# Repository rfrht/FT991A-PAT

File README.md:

# Buffered IF tap board for Panadapter / SDR in a Yaesu FT-991-A

## Instructions, tests, pictures and full documentation: Check the [Wiki](https://github.com/rfrht/FT991A-PAT/wiki)

## Yaesu FT-991/A Custom Panoramic Adapter Buffered TAP Board for external SDR / Spectrum Analyser

This project is a remix of OE2DOR's [perfect and neatly crafted](https://raw.githubusercontent.com/Lightning1984/FT991A-PAT/PAT-Light/Design/FT991-PAT_Installed.jpg) FT-991/A Panadapter board with a high impedance IF tap, in order to disturb to a [minimum](https://youtu.be/yeTeMTJRBIg) the radio sensitivity.

This design is compatible with both A and non-A FT-991 transceivers.

The objective is to actually **lodge** a RTL-SDR **inside** a FT-991/A, with no extra cables coming off the radio.

The schematics are in Autodesk Eagle EDA format. Check the [Schematic](Schematic) folder. The [Design](Design) folder contains the ready to print Gerber files, images and some ancillary material.

The project genesis and some discussion are logged on QRZ Forum: [A FT-991/A IF tap for Panadapter / RTL-SDR inside the radio](https://forums.qrz.com/index.php?threads/hard-hack-embedding-a-sdr-in-ft-991a-need-rf-designers-review.650840/). If you need to ask questions, either file a Github Issue (preferred) or use the QRZ Forum.

If you are interested in build your own, [click here to download the Gerber](Design/board-gerbers.zip) and order in your favourite PCB Fab (like [JLCPCB](https://jlcpcb.com/quote), super cheap, good quality and $0 shipping on first order). **Ensure to read the [Wiki](https://github.com/rfrht/FT991A-PAT/wiki)**.

### Notes:

* The board (5 samples) costed $2 in [jlcpcb.com](https://jlcpcb.com/quote).
* The [parts](Design/bom-ft991-panadapter.csv) costs around $20 in Digi-Key.
* The IF signal is wide open, spanning the radio's [preselector filter range](/rfrht/FT991A-PAT/wiki/appendix-preselector-rx-stage-characteristics). With that comes also a problem: Very strong signals in passband might spew images through the spectrum in your SDR. Use the RTL-SDR RX gain to counteract.
* There's a Full Version with some extra bells and whistles (more details in the Wiki). Use the Branch "Rev-R-Full".

### Changelog:
Check [Here](CHANGELOG.md)

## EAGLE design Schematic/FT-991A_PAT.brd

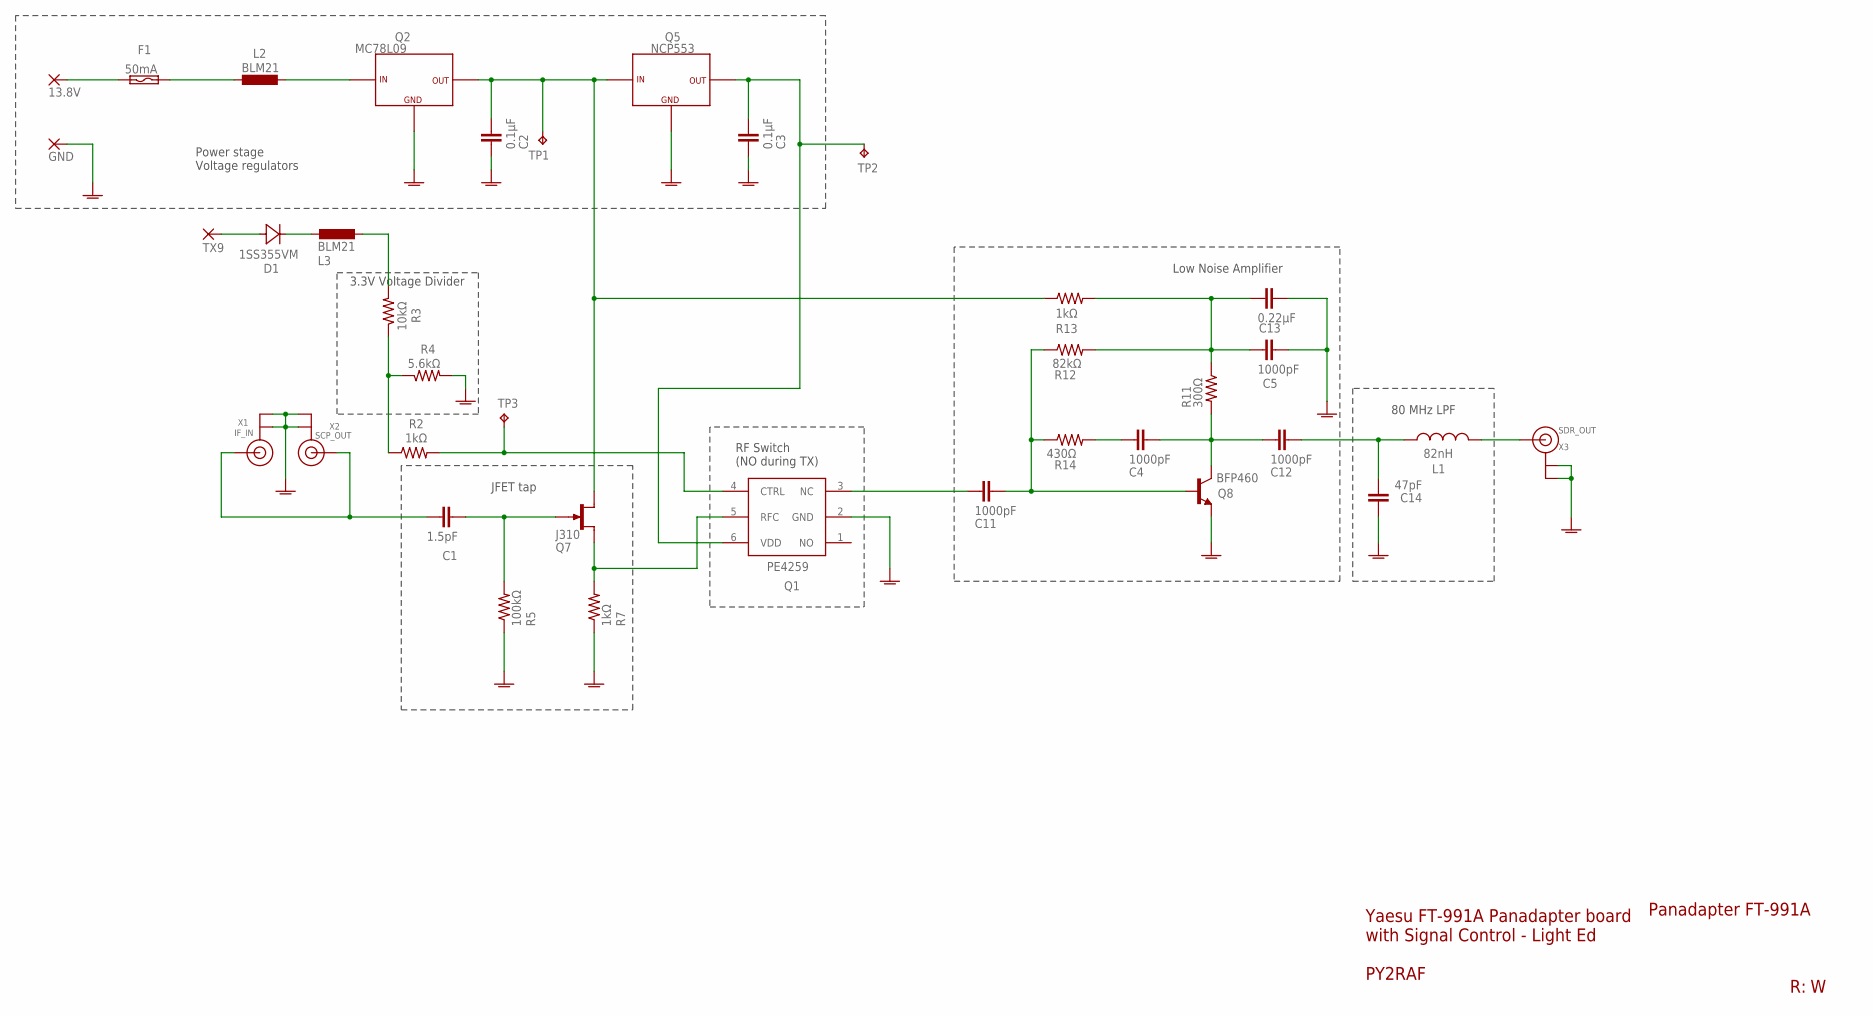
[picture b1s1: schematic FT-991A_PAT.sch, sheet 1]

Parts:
13.8V: 13.8V; SMD1,27-2,54
C1: 1.5pF; 0805
C2, C3: 0.1µF; 1206
C4, C5, C11, C12: 1000pF; 0805
C13: 0.22µF; 0805
C14: 47pF; 0805
D1: 1SS355VM; SOD-323
F1: 50mA; FUSE-1206
GND: GND; SMD1,27-2,54
L1: 82nH; 0805
L2, L3: BLM21; 0805
PAD3: TX9; SMD1,27-2,54
Q1: PE4259; SC-70
Q2: MC78L09; SOIC8
Q5: NCP553; SC-82AB
Q7: J310; SOT23-3
Q8: BFP460; SOT343R
R2, R7, R13: 1kΩ; 1206
R3: 10kΩ; 1206
R4: 5.6kΩ; 1206
R5: 100kΩ; 1206
R11: 300Ω; 1206
R12: 82kΩ; 1206
R14: 430Ω; 1206
TP1: 9V; B1,27
TP2, TP3: 3V; B1,27
X1: IF_IN; U.FL
X2: SCP_OUT; U.FL
X3: SDR_OUT; U.FL

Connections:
3V: C3.1, Q1.6 (VDD), Q5.3 (OUT), TP2.TP
9V: C2.1, Q2.1 (OUT), Q5.2 (IN), Q7.2 (S), R13.1, TP1.TP
AC-FB: C4.P$1 (1), R14.2
COLL-LOAD: C5.P$1 (1), C13.P$1 (1), R11.1, R12.2, R13.2
FINAL: L1.P$2 (2), X3.3 (SIGNAL)
GNDA: C2.2, C3.2, C5.P$2 (2), C13.P$2 (2), C14.P$1 (1), GND.1, Q1.2 (GND), Q2.2 (GN), Q2.3 (GN), Q2.6 (GN), Q2.7 (GN), Q5.1 (GN), Q8.1 (E), Q8.3 (E), R4.2, R5.1, R7.1, X1.1 (GND), X1.2 (GND), X2.1 (GND), X2.2 (GND), X3.1 (GND), X3.2 (GND)
IF-IN: C1.P$1 (1), X1.3 (SIGNAL), X2.3 (SIGNAL)
JFET-IN: C1.P$2 (2), Q7.3 (G), R5.2
JFET-OUT: Q1.5 (RFC), Q7.1 (D), R7.2
LNA-IN: C11.P$2 (2), Q8.4 (B), R12.1, R14.1
LNA-OUT: C4.P$2 (2), C12.P$1 (1), Q8.2 (C), R11.2
LPF-80M: C12.P$2 (2), C14.P$2 (2), L1.P$1 (1)
unnamed: R2.1, R3.1, R4.1
unnamed: L3.P$2 (2), R3.2
unnamed: L2.P$1 (1), Q2.8 (IN)
unnamed: 13.8V.1, F1.1
unnamed: F1.2, L2.P$2 (2)
unnamed: D1.C, L3.P$1 (1)
SW-OUT: C11.P$1 (1), Q1.3 (NC)
SW_FLIP: Q1.4 (CTRL), R2.2, TP3.TP
TX9: D1.A, PAD3.1

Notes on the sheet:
Panadapter FT-991A
PY2RAF
Yaesu FT-991A Panadapter board with Signal Control - Light Ed
3.3V Voltage Divider
Low Noise Amplifier
Power stage Voltage regulators
RF Switch (NO during TX)
JFET tap
80 MHz LPF

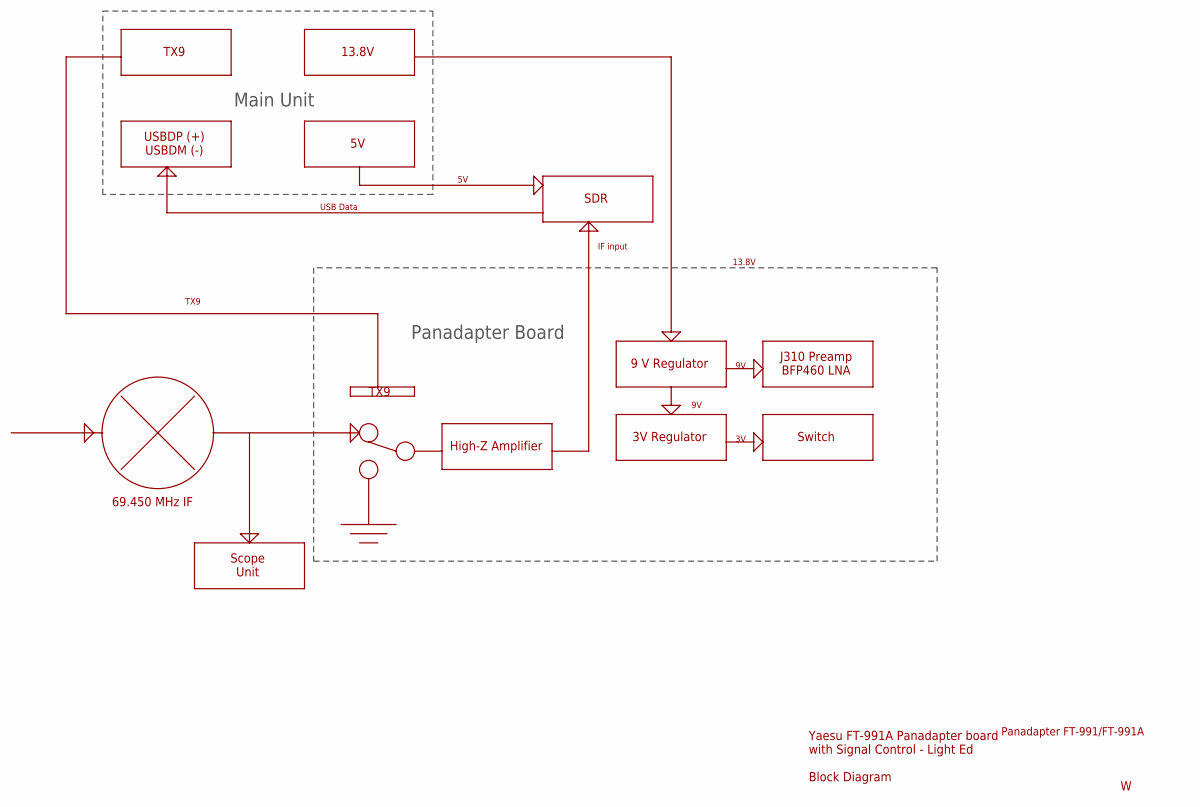
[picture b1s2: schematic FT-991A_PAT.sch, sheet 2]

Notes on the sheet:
Scope Unit
TX9
69.450 MHz IF
SDR
13.8V
Main Unit
Panadapter Board
IF input
Panadapter FT-991/FT-991A
Yaesu FT-991A Panadapter board with Signal Control - Light Ed Block Diagram
USBDP (+) USBDM (-)
USB Data
High-Z Amplifier
9 V Regulator
3V Regulator
J310 Preamp BFP460 LNA
Switch

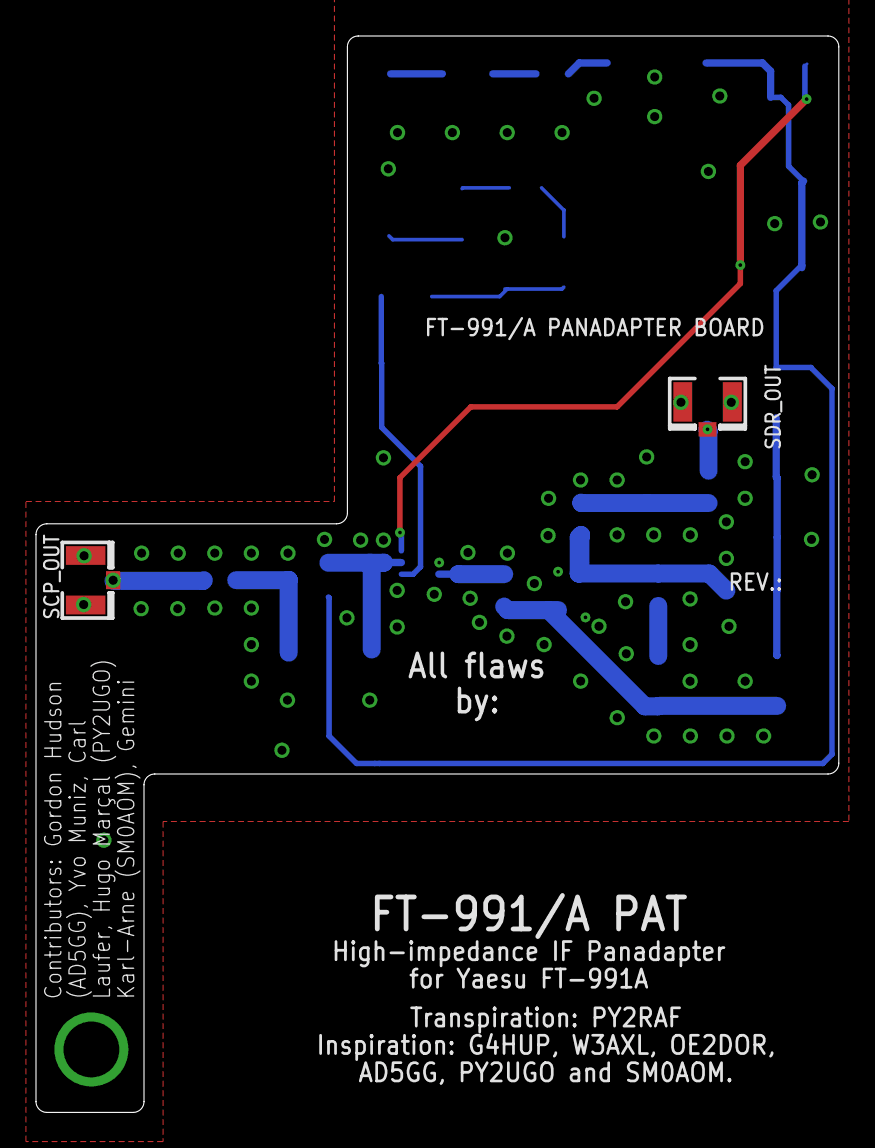
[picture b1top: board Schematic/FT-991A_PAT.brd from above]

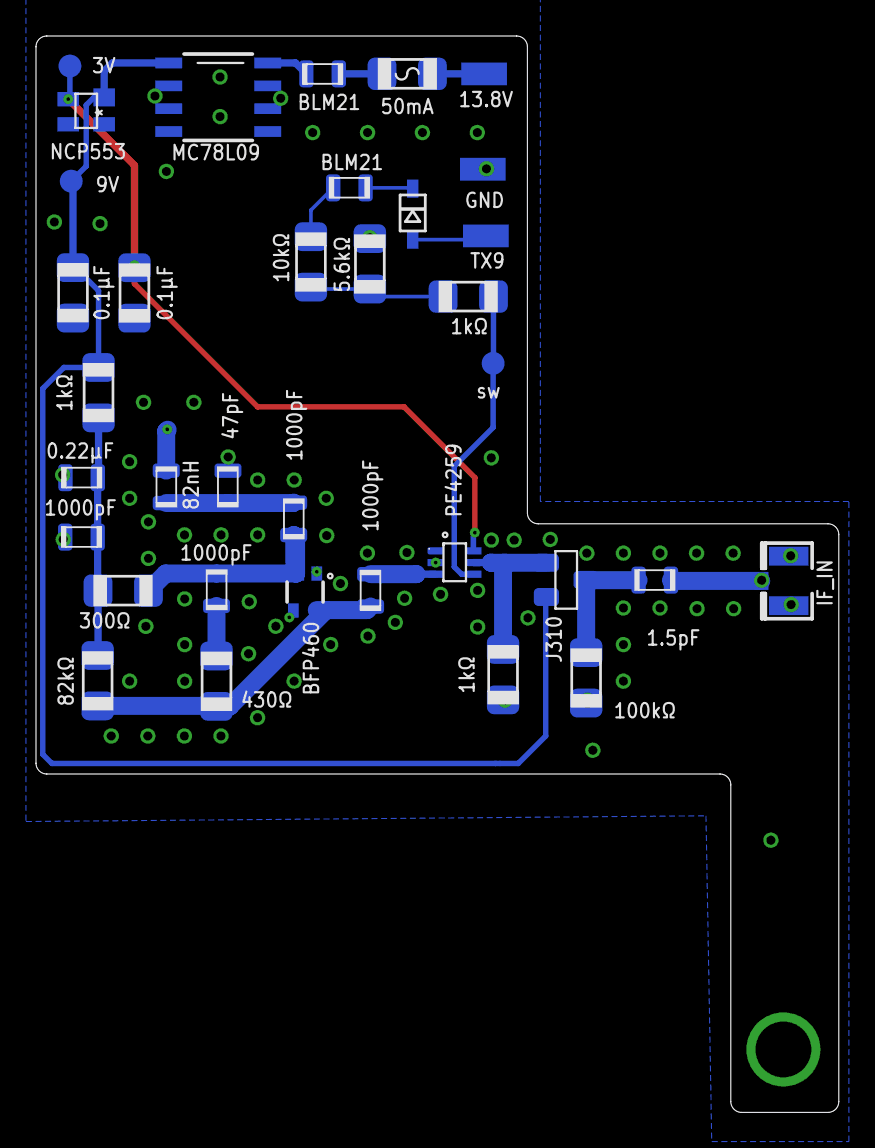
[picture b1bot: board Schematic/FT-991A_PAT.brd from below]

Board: 2 copper layers, 44.6 x 59.8 mm, 37 parts (35 on the bottom side), 21 nets.

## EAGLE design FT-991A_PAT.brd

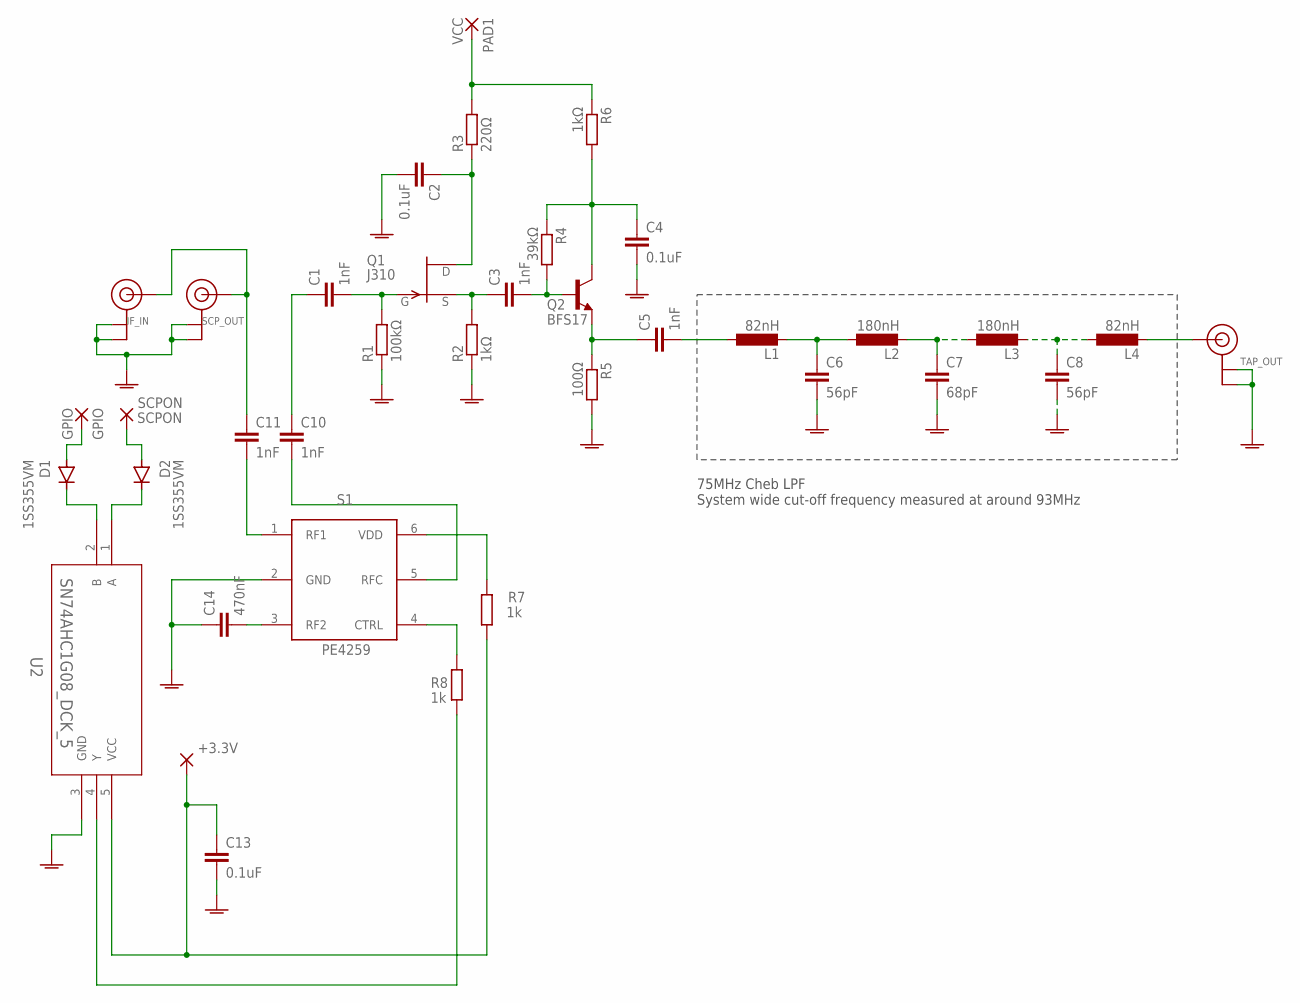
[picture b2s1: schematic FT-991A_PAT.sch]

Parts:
+3.3V: WIREPADSMD1,27-254; SMD1,27-2,54
C1, C3, C5, C10, C11: 1nF; C0805K
C2, C4, C13: 0.1uF; C0805K
C6, C8: 56pF; C0805K
C7: 68pF; C0805K
C14: 470nF; C0805K
D1, D2: 1SS355VM; SOD323-W
GPIO: GPIO; SMD1,27-2,54
L1, L4: 82nH; L0805
L2, L3: 180nH; L0805
PAD1: VCC; SMD2,54-5,08
Q1: J310; SOT23
Q2: BFS17; SOT23
R1: 100kΩ; R0805
R2: 1kΩ; R0805
R3: 220Ω; R0805
R4: 39kΩ; R0805
R5: 100Ω; R0805
R6: 1kΩ; R1206
R7, R8: 1k; R0805
S1: PE4259; SC-70
SCPON: SCPON; SMD1,27-2,54
TAP_OUT: TAP_OUT; U.FL
U2: SN74AHC1G08_DCK_5; DCK5
X1: SCP_OUT; U.FL
X2: IF_IN; U.FL

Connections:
GNDA: C2.2, C4.2, C6.2, C7.2, C8.2, C13.2, C14.1, R1.1, R2.1, R5.2, S1.2 (GND), TAP_OUT.1 (GND), TAP_OUT.2 (GND), U2.3 (GND), X1.1 (GND), X1.2 (GND), X2.1 (GND), X2.2 (GND)
unnamed: C5.1, Q2.2 (E), R5.1
unnamed: C5.2, L1.1
unnamed: C6.1, L1.2, L2.1
unnamed: C3.2, Q2.1 (B), R4.2
unnamed: C3.1, Q1.2 (S), R2.2
unnamed: C1.2, Q1.3 (G), R1.2
unnamed: C11.1, X1.3 (SIGNAL), X2.3 (SIGNAL)
unnamed: PAD1.1, R3.2, R6.1
unnamed: C2.1, Q1.1 (D), R3.1
unnamed: C4.1, Q2.3 (C), R4.1, R6.2
unnamed: C7.1, L2.2, L3.1
unnamed: L4.2, TAP_OUT.3 (SIGNAL)
unnamed: C8.1, L3.2, L4.1
unnamed: C1.1, C10.1
unnamed: C10.2, S1.5 (RFC)
unnamed: D1.A, GPIO.1
unnamed: D1.C, U2.2 (B)
unnamed: D2.A, SCPON.1
unnamed: R8.2, S1.4 (CTRL)
unnamed: D2.C, U2.1 (A)
unnamed: C11.2, S1.1 (RF1)
unnamed: R8.1, U2.4 (Y)
unnamed: C14.2, S1.3 (RF2)
VCC: +3.3V.1, C13.1, R7.1, U2.5 (VCC)
VDD: R7.2, S1.6 (VDD)

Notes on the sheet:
75MHz Cheb LPF System wide cut-off frequency measured at around 93MHz

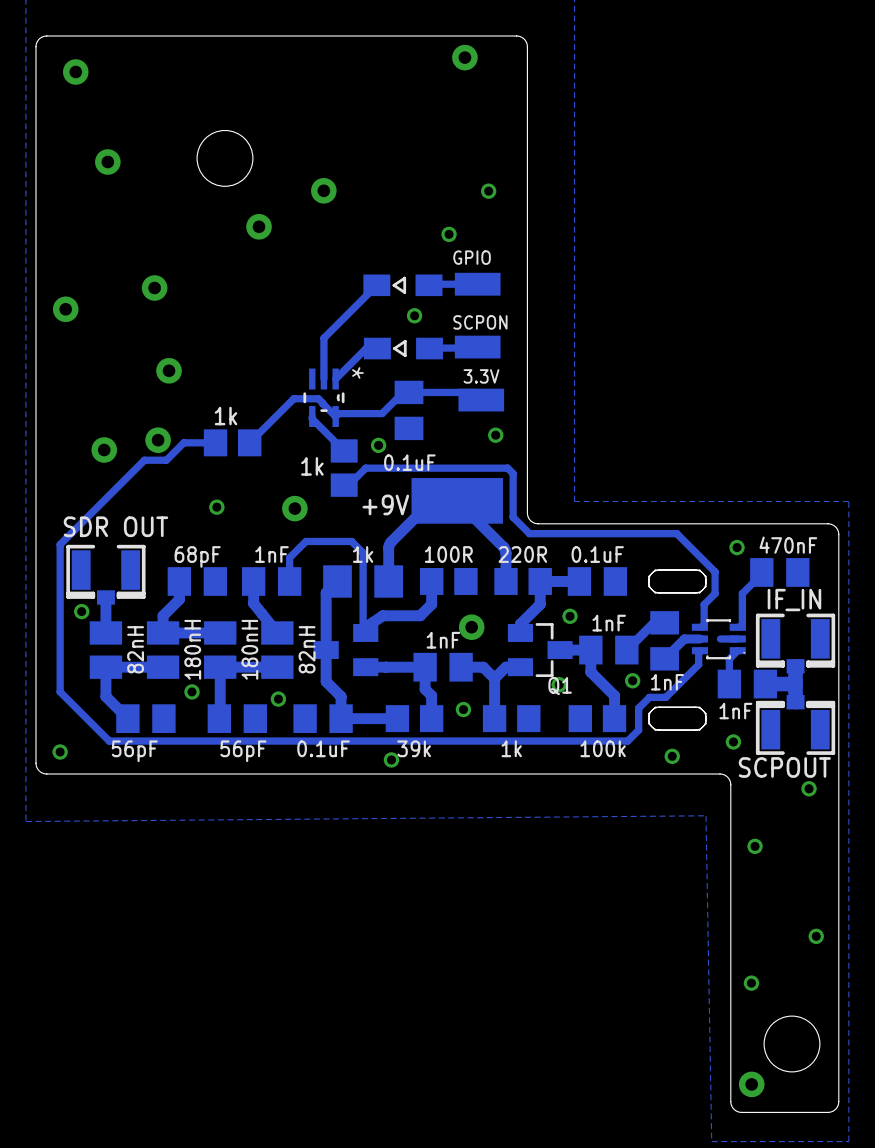
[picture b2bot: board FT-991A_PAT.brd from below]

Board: 2 copper layers, 44.6 x 59.8 mm, 37 parts (37 on the bottom side), 26 nets.

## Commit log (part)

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2018-05-21 Removed old sch/brd files
2018-05-21 New Board layout and schematic files added
2019-03-25 Revision D
    - Reusing OE2DOR design
    - Added a AND gate and a switch to be able to control the IF traffic
    to the dongle
2019-03-25 Revision E
    - Now sports a RF switch (PE4259) instead of a regular Analog switch
    (was: SN74LVC1G66);
    * Also contains its resistors as per reference design;
    - Changed voltage from 5V to 3.3V to Switch and AND port;
    - SDR output will be grounded by default when switch is in default state
    (RF 2 port) port
2019-03-27 Revision F
    * Added 1 nF capacitors in RF lines in PE4529 (except RF2, goes with a
    470 pF to GND)
    * Got rid of the VCC via which was crossing the RF line (argh)
    * Finally got the courage to change a bit the board layout and escape
    from the thin strip that I was working previously.
    * And another THANK YOU to Gordon AD5GG for his invaluable feedback and
2019-03-27 New files, correction, better schematic layout
    Still in Revision F:
    * Fixed C14 values (it is 4.7 nF and not 470 pF)
    * Cleaner and unified board layout
    * Identified properly Q1 (it is a J310)
    * A few tweaks and spam in board silk screen
    * Added project's PDF and board's PNG images
2019-03-27 Reorganized directory structure
    * Moved Schematics to Schematic folder
    * Moved parts/BOM to Design folder
    * Updated README file to reflect the changes
2019-03-27 More README edit
2019-03-28 Revision G
    Removed a lingering DC blocking 1nF capacitor after RF switch
2019-03-28 Added a PDF depicting the project overview and connections
2019-03-28 Revision G - Updated README, forgot to document the chokes
2019-03-30 Updated Parts
    * New Parts file
    * Added a Digikey-formatted BOM
    * Schematic with a few part renames, nothing noteworthy
2019-03-30 Reference to board in OSHPark
2019-04-08 Revision I
    Added:
    * RTL-SDR USB port
    * U.FL jumper cords in BOM
    * 3 power regulators in the board
    Changed:
    * Power supply: Now uses a single external 13.8V voltage source
2019-04-09 Updated OSHPark URL
2019-04-09 Set theme jekyll-theme-cayman
2019-04-11 Status update
2019-05-18 Yes it is compatible with the Non-A model
    And added info stating that the Rev. J will use the RX9 signal.
2019-05-18 Added FT-991 (non-A) IF tap point
2019-05-18 A few Readme revisions
2019-05-18 New PCB Pictures
2019-05-20 Revision K
    * Changed footprints: BOM specifies 1206, project had 0805
    - Unified everything Resistors and Capacitors in 1206
    - Inductors are 0805
    * A few routing enhancements
    * Recalculated the component indexes
    * Updated BOM to reflect the new component index
2019-05-20 A few README corrections
2019-05-24 EXPERIMENTAL: Revision L
    Long shot. In this revision:
    * Added the ability to bypass entirely the amplifier and filters
    - Selectable by RF switch (default: off)
    * Added a 3-pole Chebyshev Band-pass Filter centered at 69.450 MHz, 3
    MHz wide
    - Selectable by RF switch (default: off)
2019-05-30 Revision M
    In this revision:
    * Got rid of the USB receptacle - Too much space in a tight radio
    * Moved all GPIO pads to the upper board side
    * Added a few missing Pin 1 references
    * Renamed voltage regulators to somewhat shorter name
    * Small re-routing - 9V regulator was entangled with capacitor
2019-05-30 Updated Readme, JLCPCB fluff
2019-05-31 Removed USB jack and U.FL to SMA cables
    Not needed, won't fit in the project.
2019-06-22 Revision N - No USB
    A truckload of changes. Namely:
    * Removed the 5V regulator
    * Removed the USB provisions
    * Removed the G4HUP LPF. Reasoning: Found it of no use, since it cuts
    * the signal 24 MHz above the IF center frequency. The selectable BPF
    * suits better.
2019-06-22 Corrected BOM url
2019-06-22 README: Added link to no-USB version
2019-08-21 Better Wiki placement
2019-08-22 Revision N Finished board images
2019-08-26 Revision N updated documentation, links and Files
    And removed the BPF references.
2019-08-29 Changed video URL in Readme
2019-08-31 Added link to Parts
2019-10-05 Revision O: Moving toward golden
    Components placed, new BPF design (tips hat to Karl-Anne SM0AOM)
    Major board reorganization
2019-10-07 More Rev. O Advancements
    Reviewed Ground Plane
    Added (lots of) ground plane vias
    Renumbered parts
    Ran DRC and fixed a lot of airwires
    A few component positioning hacks
    Updated the Project Overview Block Diagram sheet
2019-10-14 Components BOM reordering
    Better readability, sorted by qty
2019-11-03 Revision O - Readme update
2019-11-03 Board: Eagle image while board doesn't get assembled.
2019-11-24 Light Edition: Initial commit
    Presenting... Light Edition!
    * A slimmer BoM
    * ... $ SAVINGS!
    * Less insertion loss, moar GAIN
    * Less building time
    * Essentials for the win.
2019-11-24 Small Readme correction
2019-11-25 Light Ed.: Small PCB Correction
    * Repositioned a capacitor and straightened a power line
    * Also cleaned a few PCB DRC Warnings
2019-11-25 Added reference to Light Edition in Master Readme
2020-06-20 Fixed capacitor unit
2020-06-20 New images
2020-06-21 Updated Diagram
2020-06-21 Updated Schematic to reflect the Diagram
2020-06-21 Updated Schematics - new board layout
2020-06-28 Starring: Revision P
    * Repositioned the SDR Out port to right above the DC block cap
    * Changed RF switch layout - now IF input uses the RF switch's `RFC`
    port instead of RF2 - It seems that the PE4259's `RF{N}` port gets in
    a grounded state instead of just reflecting out the data when not
    selected / active
    * Got rid of the "Grounding" in RF1 port; that's not necessary
2020-06-28 Removed 4.7 nF capacitor (C2) used in RF Ground
    This capacitor no longer exists, due to PE4259 flipping.
2020-06-28 Minor Readme note
2020-06-28 Starring: Revision P, Full Version
    * Changed RF switch layout - now IF input uses the RF switch's `RFC`
    port instead of RF2 - It seems that the PE4259's `RF{N}` port gets in
    a grounded state instead of just reflecting out the data when the port
    is not selected/active
    * Got rid of the "Grounding" in RF1 port; that's not necessary
    because... Above
2020-06-28 Reorganized BOM, removed BPF design file
    No need for the BPF file - this verson has no BPF.
    Reorganized the BOM - just meaningful component placement.
2020-06-28 Updated board pictures
2020-06-28 Board: Added test pads
    Added test pads for 9V, 3V and RF Switch.
2020-07-01 Ground plane and board design change
    Moved a power line to the board border instead traveling by the middle
    of the board, essentially (unnecessarily) splitting in two the board
    ground planes.
    New gerber.
2020-07-05 Updated final PCB Images
2020-07-05 Updated PCB layout files
2020-08-10 Starring: Revision Q
    * Changed 1000pF caps to a 0805 footprint and an low ESL variant for
    better RF performance
    * A lot of re-routing; moving non-RF circuits to other parts of the
    board
    * Better ground plane
    * Better Silk-Screen Pin 1 markings for Power regulators
2020-08-11 Fixed Bill of Materials
    Was broken when merged.
2020-08-11 BOM: Fixed bill of materials
    Was broken when merging
2020-10-10 Few other enhancements
    - Reversed J310 JFET for better signal routing
    * Avoiding signal xing
    * And taking advantage of J310 source & drain interchangeability
    - More routing optimization
2020-10-10 Minor routing hacks
    - Replaced J310 JFET
    * Taking full advantage of its Source and Drain interchangeability
    * Avoiding some signal track xing
    - And more routing changes.
2020-10-11 Changed J310 to an active variant
    Reported in #13 - Component went to obsolete state.
    Thanks to @wgxdz for pointing.
2020-10-21 Rev. Q more enhancements
    - Changed two resistors in Amplifier chain in order to get some more
    gain - See Issue 14
    - Updated BOM in order to reflect this change
    - Added a ground pad, that's useful when troubleshooting and the lack
    of it bit my butt a number of times
2020-10-23 Moved Changelog to separate file
    In order to de-clutter Readme file.
2020-11-30 Few general (tentative) improvements
    * Larger ground exposed ground pad near at the screw
    * Changed pad for RF components to a rounded layout
    * Enlarged the RF wire signal, in order to reduce the internal signal
    impedance
    * Better component silk screen
2021-02-21 Rev. Q: Rew improvements
    * Moved TX9 signal treatment compoments from board lid to larger board
    * Changed fuse silk screen
2021-04-13 Starring: Revision R
    Check CHANGELOG.md for new features.
2021-10-03 Board notes: Fixed wrong revision note
    Silkscreen had Rev. Q - this is Rev. R.
2022-01-28 Changelog: Added new Rev R changes
2022-01-28 Changelog: Rev R larger pads
2022-01-28 Revision R Update
    * Larger pads for Diodes and NCP553, easing the soldering process
    * Also: Updated the PDF files.
2022-01-28 Christening Rev. R
    * New PDF files
    * Voltage regulator re-routing
    * Larger NCP533 and Diode pads
    * Fixed some BOM errors
    * Removed some old files
    * Added Eagle Library file
2022-01-29 Readme: Updated some wrong links
    And also added a note about the Full Version
2022-01-29 Readme: some more extra information.
    And also testing commit signing.
2022-03-07 Readme: Better description for Design folder
2022-03-16 BOM: Changed Ferrite Bead part
    Replaced the Murata choke with a Bourns one, due to Murata unavailability.
2022-04-12 Rev. S: Replaced 2SC5086 with BFR193F
    * Replaced 2SC5086 with BFR193F amplifier, since 2SC5086 is now EOL
    * Added a RF choke (L7) to avoid signal feedback propagating in 3V line
2022-05-23 Fixed part number for 100K R
2022-07-19 Rev. S: New RF switch actuation
    * New RF switch design - now uses an analog switch to flip the RF switch.
    While this added new parts (1 switch and two resistors) and extra
    complexity, this actuation format is industry-standard and allows
    for substitutes of PE4259 (which is unobtanium as of now).
    * New component in library (NLAS4599)
2022-08-03 Test updating Readme File
2023-11-16 BOM: Updated J310 part number
    That one is available at Digikey
2023-11-16 Update README.md
    Small disclaimer
2023-11-16 Update bom-ft991-panadapter.csv
    Changed the switch part number, the original went EOL
2023-11-16 Update bom-ft991-panadapter.csv
    Changed J310 part number to an available one
2023-11-16 Update bom-ft991-panadapter.csv
    Another RF switch variant, currently stocked
2023-11-16 Update bom-ft991-panadapter.csv
    Fixed 100k resistor PN
    Changed RF switch to a compatible part (PE42421)
    Changed J310 part to an available variant
2024-11-19 Announcing: Revision U
    Featuring:
    * A properly matched BFR193F transistor, yielding 7 dB of gain,
    surpassing 2SC5086
    * Larger pads for BFR193F
    * Few routing improvements, larger wires
    * Removed a via near the 3V regulator, didnt help a lot and was
2024-11-19 Update CHANGELOG.md
    Rev. U note
2024-11-20 BOM: Wrong value for resistor
2024-12-10 Update bom-ft991-panadapter.csv
    Fixed diode DigiKey PN
2024-12-20 Improved PE4259
    Now NO/NC instead of "RF1" and "RF2". bah.
2024-12-22 Library: Added NOR 74HC part
2024-12-26 Updating PDF schematic
2024-12-26 Updating Schematic and Board
2024-12-26 Updating library
    New part: BFP460
2024-12-26 Library: New part BFP460
    New part
2024-12-26 Library: New part BFP460
2025-01-07 Library: Added Tayo 1207 footprint/component for inductors
2025-02-18 Gerber: updating gerber file with updated BFR460
2025-07-09 Library: New component
    Added SMA Edge connector to the library.
    Compatible with 2057-RF2-145A-T-17-50-G-HDW-ND
2025-07-10 Library: New component (single-header jumper)
    Also, changed Fuse to include the component value (was disabled in library)
2025-08-31 Library: Improved SN74 footprint
    * Changed SN74-AND to use SC-70 footprint instead of DCK5
2026-03-01 Library: Fixed UMD5N pinout
2026-05-06 Library: Added MIC5205
    In use by SignalSurge.

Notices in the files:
FT-991A_PAT.sch:
COPYRIGHT: PY2RAF
